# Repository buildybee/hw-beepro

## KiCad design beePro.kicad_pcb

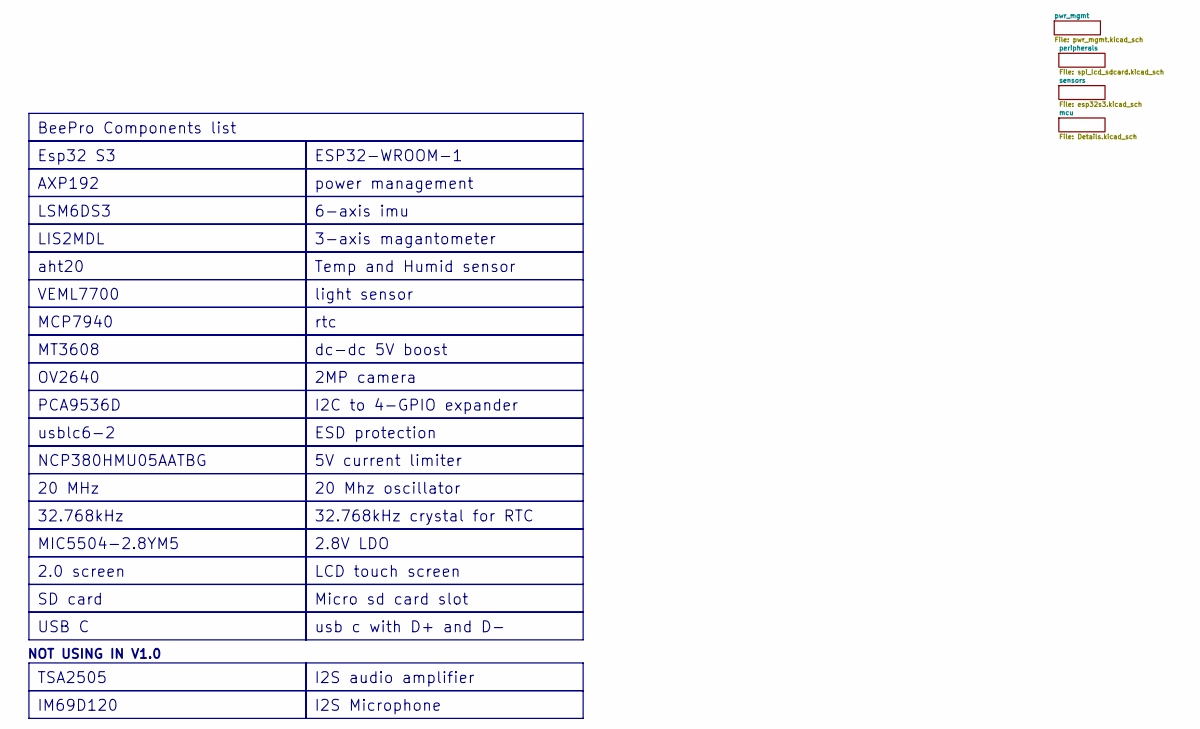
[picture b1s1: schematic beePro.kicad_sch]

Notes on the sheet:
NOT USING IN V1.0
20 Mhz oscillator
OV2640
2.8V LDO
MIC5504-2.8YM5
BeePro Components list
USB C
VEML7700
20 MHz
Micro sd card slot
I2S Microphone
rtc
5V current limiter
power management
light sensor
TSA2505
SD card
I2C to 4-GPIO expander
NCP380HMU05AATBG
LIS2MDL
MCP7940
Esp32 S3
AXP192
I2S audio amplifier
32.768kHz
2.0 screen
usb c with D+ and D-
32.768kHz crystal for RTC
ESP32-WROOM-1
3-axis magantometer
Temp and Humid sensor
6-axis imu
PCA9536D
aht20
ESD protection
MT3608
IM69D120
usblc6-2
2MP camera
dc-dc 5V boost

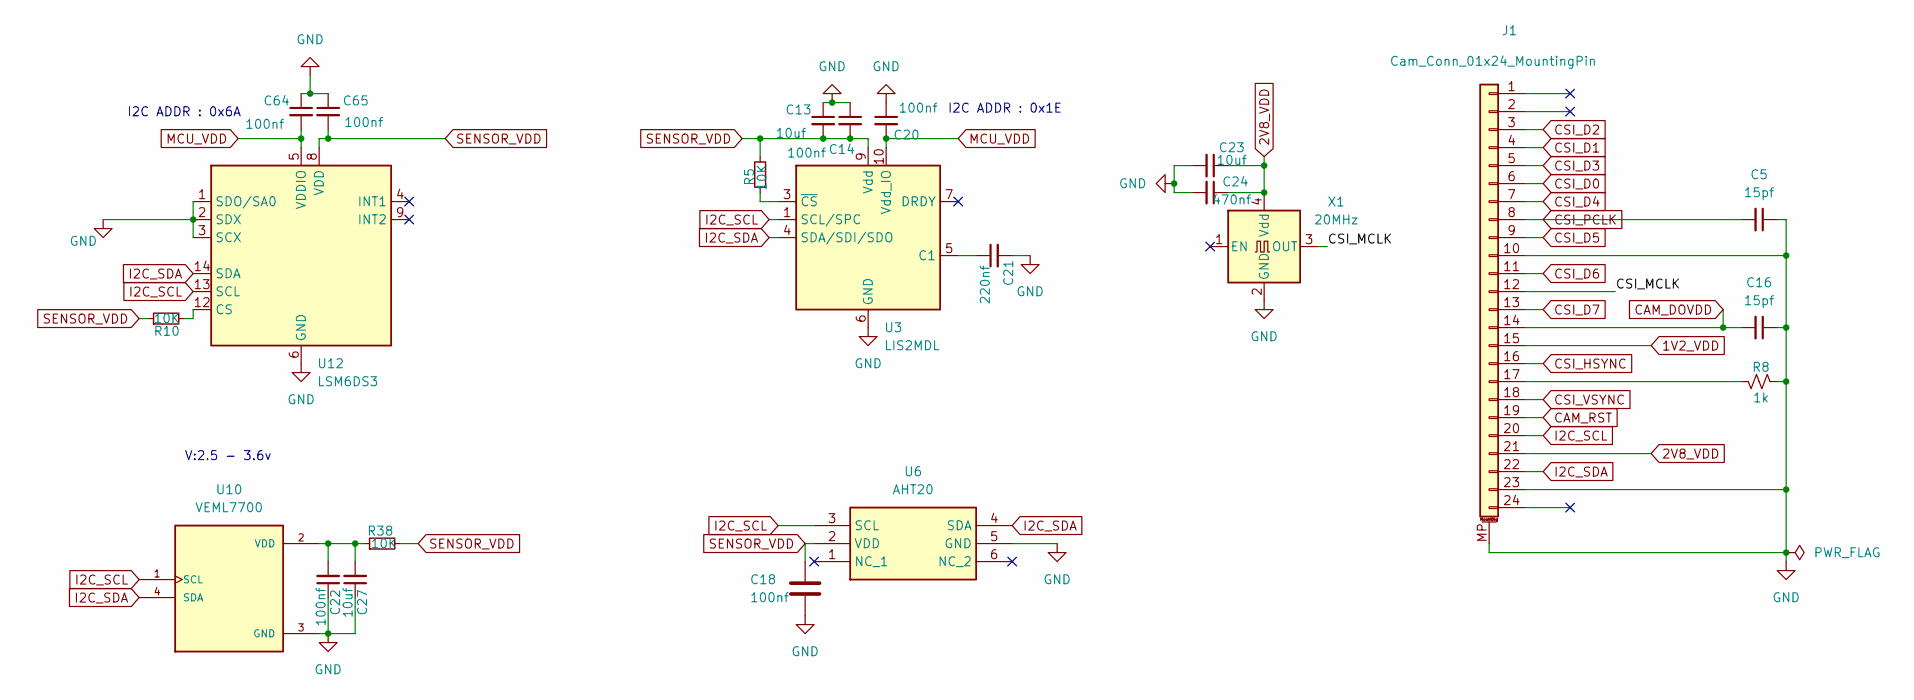
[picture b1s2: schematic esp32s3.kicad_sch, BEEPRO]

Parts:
C5, C16: 15pf; C_0603_1608Metric_Pad1.08x0.95mm_HandSolder
C13, C23, C27: 10uf; C_0603_1608Metric_Pad1.08x0.95mm_HandSolder
C14, C18, C20, C22, C64, C65: 100nf; C_0603_1608Metric_Pad1.08x0.95mm_HandSolder
C21: 220nf; C_0603_1608Metric_Pad1.08x0.95mm_HandSolder
C24: 470nf; C_0603_1608Metric_Pad1.08x0.95mm_HandSolder
J1: Cam_Conn_01x24_MountingPin; Hirose_FH12-24S-0.5SH_1x24-1MP_P0.50mm_Horizontal
R5, R10, R38: 10K; R_0603_1608Metric_Pad0.98x0.95mm_HandSolder
R8: 1k; R_0603_1608Metric_Pad0.98x0.95mm_HandSolder
U3: LIS2MDL; LGA-12_2x2mm_P0.5mm
U6: AHT20; Manufacturer_Part_Number AHT20
U10: VEML7700; XDCR_VEML7700-TR; PARTREV 1.6
U12: LSM6DS3; LGA-14_3x2.5mm_P0.5mm_LayoutBorder3x4y
X1: 20MHz; Oscillator_SMD_Abracon_ASE-4Pin_3.2x2.5mm

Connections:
1V2_VDD: J1.15; also elsewhere on the board
2V8_VDD: C23.1, C24.1, J1.21, X1.4 (Vdd); also elsewhere on the board
/sensors/CSI_MCLK: J1.12, X1.3 (OUT)
CAM_DOVDD: C5.1, C13.1, C13.2, C14.1, C14.2, C16.1, C16.2, C18.1, C18.2, C20.1, C21.2, C22.1, C23.2, C24.2, C27.1, C64.1, C65.1, C65.2, J1.10, J1.14, J1.23, J1.MP (MountPin), R5.2, R8.1, R10.1, R38.2, U3.6 (GND), U3.8 (GND), U3.9 (Vdd), U6.2 (VDD), U6.5 (GND), U10.3 (GND), U12.1 (SDO/SA0), U12.2 (SDX), U12.3 (SCX), U12.6 (GND), U12.7 (GND), U12.8 (VDD), X1.2 (GND); also elsewhere on the board
CAM_RST: J1.19
CSI_D0: J1.6; also elsewhere on the board
CSI_D1: J1.4; also elsewhere on the board
CSI_D2: J1.3; also elsewhere on the board
CSI_D3: J1.5; also elsewhere on the board
CSI_D4: J1.7; also elsewhere on the board
CSI_D5: J1.9; also elsewhere on the board
CSI_D6: J1.11; also elsewhere on the board
CSI_D7: J1.13; also elsewhere on the board
CSI_HSYNC: J1.16; also elsewhere on the board
CSI_PCLK: C5.2, J1.8; also elsewhere on the board
CSI_VSYNC: J1.18; also elsewhere on the board
I2C_SCL: J1.20, U3.1 (SCL/SPC), U6.3 (SCL), U10.1 (SCL), U12.13 (SCL); also elsewhere on the board
I2C_SDA: J1.22, U3.4 (SDA/SDI/SDO), U6.4 (SDA), U10.4 (SDA), U12.14 (SDA); also elsewhere on the board
MCU_VDD: C20.2, C64.2, U3.10 (Vdd_IO), U12.5 (VDDIO); also elsewhere on the board
unnamed: J1.17, R8.2
unnamed: C21.1, U3.5 (C1)
unnamed: R5.1, U3.3 (~CS)
unnamed: C22.2, C27.2, R38.1, U10.2 (VDD)
unnamed: R10.2, U12.12 (CS)

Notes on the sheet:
V:2.5 - 3.6v
I2C ADDR : 0x6A
I2C ADDR : 0x1E

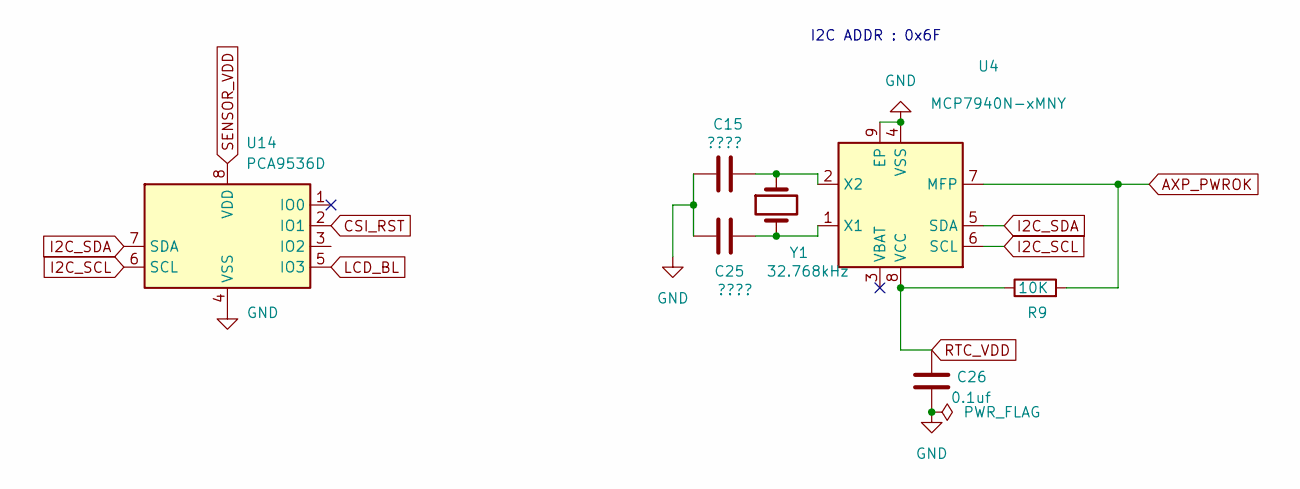
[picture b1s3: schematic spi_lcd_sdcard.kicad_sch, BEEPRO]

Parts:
C15, C25: ????; C_0603_1608Metric_Pad1.08x0.95mm_HandSolder
C26: 0.1uf; C_0603_1608Metric_Pad1.08x0.95mm_HandSolder
R9: 10K; R_0603_1608Metric_Pad0.98x0.95mm_HandSolder
U4: MCP7940N-xMNY; DFN-8-1EP_3x2mm_P0.5mm_EP1.36x1.46mm
U14: PCA9536D; SOIC-8_3.9x4.9mm_P1.27mm
Y1: 32.768kHz; Crystal_SMD_3215-2Pin_3.2x1.5mm

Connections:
AXP_WAKEUP: R9.2, U4.7 (MFP); also elsewhere on the board
CAM_DOVDD: C15.2, C25.1, C26.2, U4.4 (VSS), U4.9 (EP), U14.4 (VSS), U14.8 (VDD); also elsewhere on the board
CSI_RST: U14.2 (IO1)
I2C_SCL: U4.6 (SCL), U14.6 (SCL); also elsewhere on the board
I2C_SDA: U4.5 (SDA), U14.7 (SDA); also elsewhere on the board
LCD_RST: U14.3 (IO2)
unnamed: C25.2, U4.1 (X1), Y1.2
unnamed: C15.1, U4.2 (X2), Y1.1
RTC_VDD: C26.1, R9.1, U4.8 (VCC); also elsewhere on the board

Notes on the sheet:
I2C ADDR : 0x6F

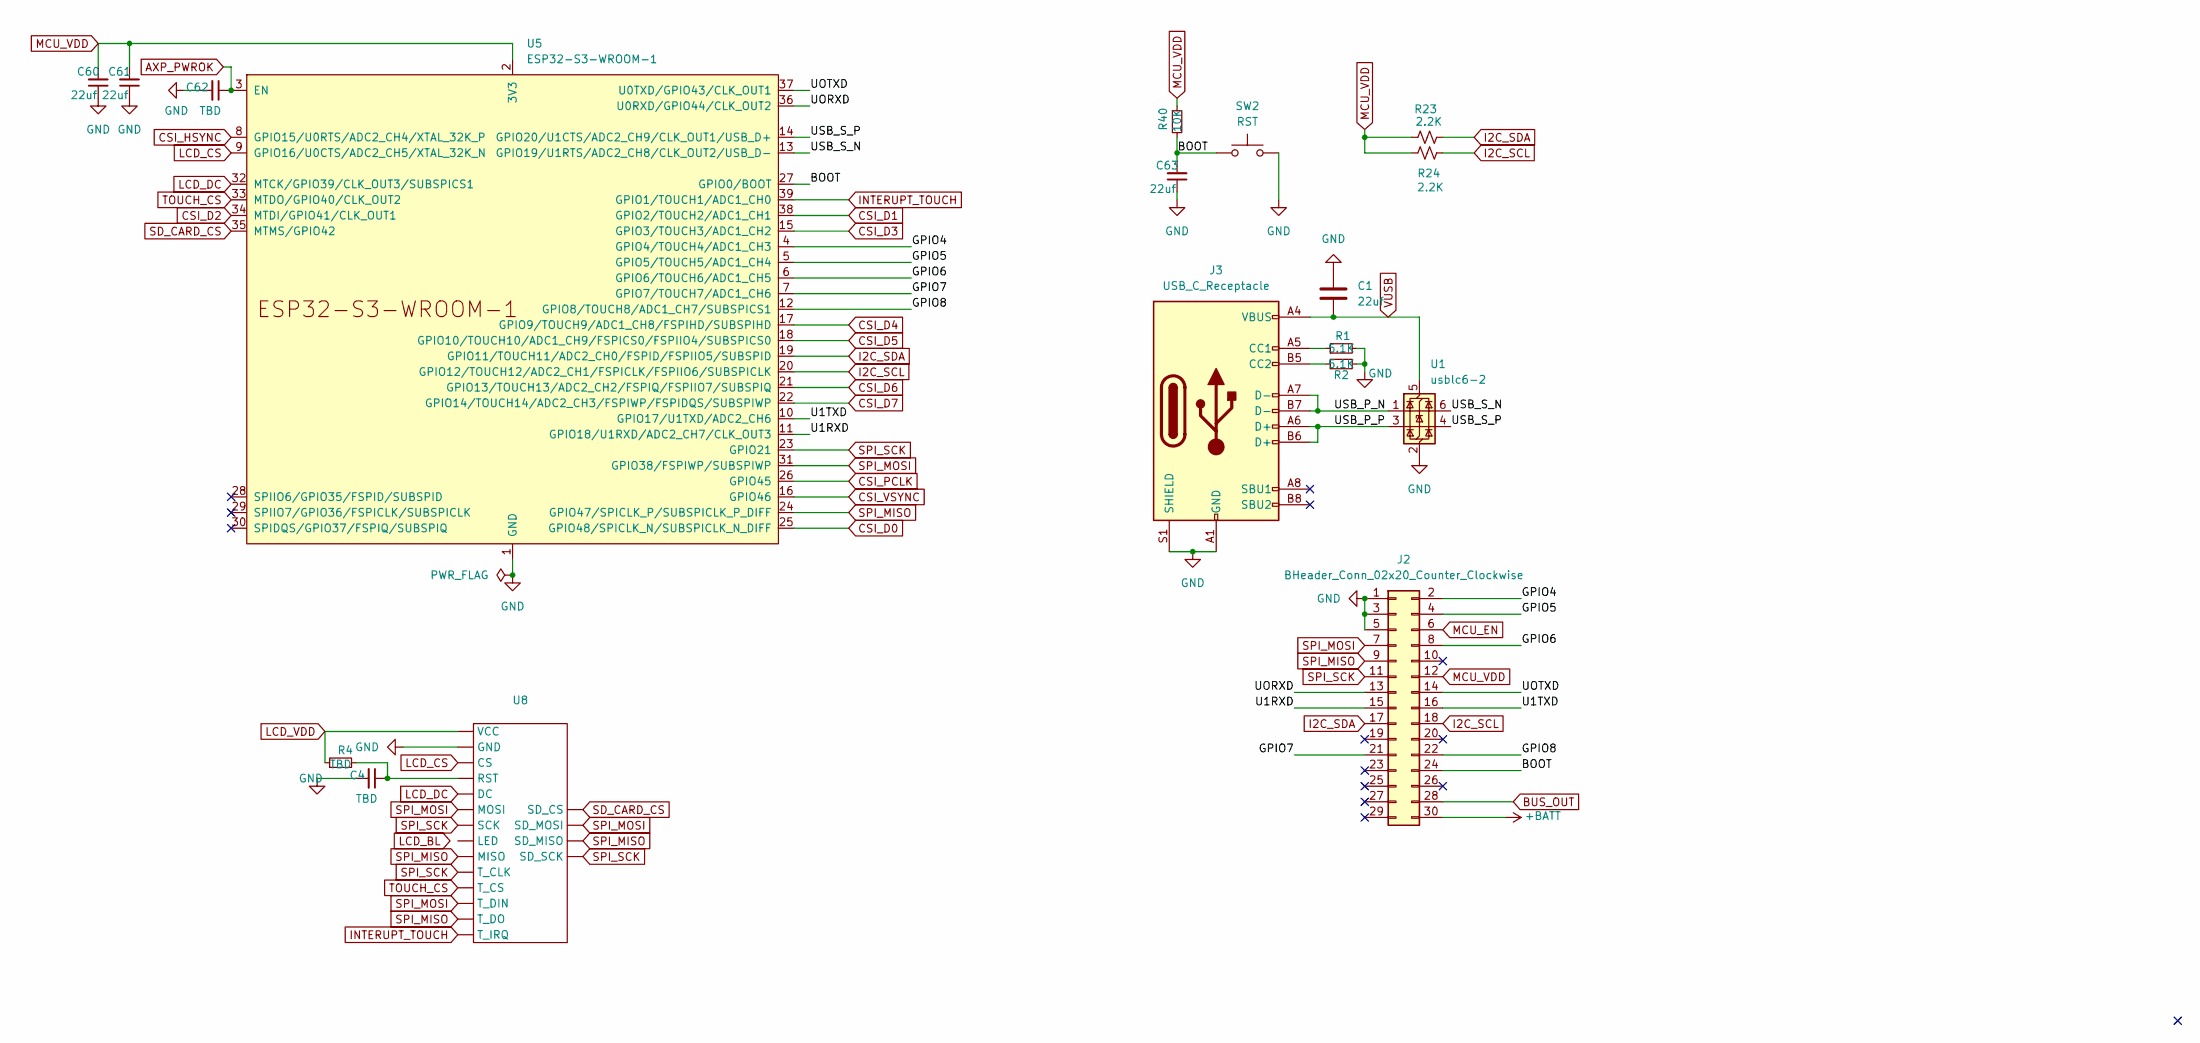
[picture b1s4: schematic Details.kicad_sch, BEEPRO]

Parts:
C1, C60, C61, C63: 22uf; C_0603_1608Metric_Pad1.08x0.95mm_HandSolder
C4, C62: TBD; C_0603_1608Metric_Pad1.08x0.95mm_HandSolder
J2: BHeader_Conn_02x20_Counter_Clockwise; PinSocket_2x15_P2.54mm_Vertical
J3: USB_C_Receptacle; USB_C_Receptacle_GCT_USB4110
R1, R2: 5.1K; R_0603_1608Metric_Pad0.98x0.95mm_HandSolder
R4: TBD; C_0603_1608Metric_Pad1.08x0.95mm_HandSolder
R23, R24: 2.2K; R_0603_1608Metric_Pad0.98x0.95mm_HandSolder
R40: 10K; R_0603_1608Metric_Pad0.98x0.95mm_HandSolder
SW2: RST; SW_SPST_PTS647_Sx38
U1: usblc6-2; SOT-23-6
U5: ESP32-S3-WROOM-1; ESP32-S3-WROOM-1U
U8: (no value)

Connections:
+BATT: J2.30; also elsewhere on the board
/mcu/BOOT: C63.2, J2.24, R40.2, SW2.1, U5.27 (GPIO0/BOOT)
/mcu/GPIO4: J2.2, U5.4 (GPIO4/TOUCH4/ADC1_CH3)
/mcu/GPIO5: J2.4, U5.5 (GPIO5/TOUCH5/ADC1_CH4)
/mcu/GPIO6: J2.8, U5.6 (GPIO6/TOUCH6/ADC1_CH5)
/mcu/GPIO7: J2.21, U5.7 (GPIO7/TOUCH7/ADC1_CH6)
/mcu/GPIO8: J2.22, U5.12 (GPIO8/TOUCH8/ADC1_CH7/SUBSPICS1)
/mcu/U1RXD: J2.15, U5.11 (GPIO18/U1RXD/ADC2_CH7/CLK_OUT3)
/mcu/U1TXD: J2.16, U5.10 (GPIO17/U1TXD/ADC2_CH6)
/mcu/UORXD: J2.13, U5.36 (U0RXD/GPIO44/CLK_OUT2)
/mcu/UOTXD: J2.14, U5.37 (U0TXD/GPIO43/CLK_OUT1)
/mcu/USB_P_N: J3.A7 (D-), J3.B7 (D-), U1.1 (I/O1)
/mcu/USB_P_P: J3.A6 (D+), J3.B6 (D+), U1.3 (I/O2)
/mcu/USB_S_N: U1.6 (I/O1), U5.13 (GPIO19/U1RTS/ADC2_CH8/CLK_OUT2/USB_D-)
/mcu/USB_S_P: U1.4 (I/O2), U5.14 (GPIO20/U1CTS/ADC2_CH9/CLK_OUT1/USB_D+)
BUS_OUT: J2.28; also elsewhere on the board
CAM_DOVDD: C1.1, C4.2, C60.1, C61.1, C62.2, C63.1, J2.1, J2.3, J2.5, J3.A1 (GND), J3.A12 (GND), J3.B1 (GND), J3.B12 (GND), J3.S1 (SHIELD), R1.2, R2.2, SW2.2, U1.2 (GND), U5.1 (GND), U5.40 (GND), U5.41 (GND), U8.; also elsewhere on the board
CSI_D0: U5.25 (GPIO48/SPICLK_N/SUBSPICLK_N_DIFF); also elsewhere on the board
CSI_D1: U5.38 (GPIO2/TOUCH2/ADC1_CH1); also elsewhere on the board
CSI_D2: U5.34 (MTDI/GPIO41/CLK_OUT1); also elsewhere on the board
CSI_D3: U5.15 (GPIO3/TOUCH3/ADC1_CH2); also elsewhere on the board
CSI_D4: U5.17 (GPIO9/TOUCH9/ADC1_CH8/FSPIHD/SUBSPIHD); also elsewhere on the board
CSI_D5: U5.18 (GPIO10/TOUCH10/ADC1_CH9/FSPICS0/FSPIIO4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); also elsewhere on the board
CSI_D6: U5.21 (GPIO13/TOUCH13/ADC2_CH2/FSPIQ/FSPIIO7/S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); also elsewhere on the board
CSI_D7: U5.22 (GPIO14/TOUCH14/ADC2_CH3/FSPIWP/FSPIDQS/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); also elsewhere on the board
CSI_HSYNC: U5.8 (GPIO15/U0RTS/ADC2_CH4/XTAL_32K_P); also elsewhere on the board
CSI_PCLK: U5.26 (GPIO45); also elsewhere on the board
CSI_VSYNC: U5.16 (GPIO46); also elsewhere on the board
I2C_SCL: J2.18, R24.2, U5.20 (GPIO12/TOUCH12/ADC2_CH1/FSPICLK/FSPIIO6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); also elsewhere on the board
I2C_SDA: J2.17, R23.2, U5.19 (GPIO11/TOUCH11/ADC2_CH0/FSPID/FSPIIO5/S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); also elsewhere on the board
INTERUPT_TOUCH: U5.39 (GPIO1/TOUCH1/ADC1_CH0), U8.
LCD_CS: U5.9 (GPIO16/U0CTS/ADC2_CH5/XTAL_32K_N), U8.
LCD_DC: U5.32 (MTCK/GPIO39/CLK_OUT3/SUBSPICS1), U8.
MCU_VDD: C60.2, C61.2, J2.12, R23.1, R24.1, R40.1, U5.2 (3V3); also elsewhere on the board
unnamed: C4.1, R4.2, U8.
unnamed: J3.A5 (CC1), R1.1
unnamed: J3.B5 (CC2), R2.1
unnamed: R4.1, U8.
unnamed 78: C62.1, U5.3 (EN); also elsewhere on the board
SD_CARD_CS: U5.35 (MTMS/GPIO42), U8.
SPI_MISO: J2.9, U5.24 (GPIO47/SPICLK_P/SUBSPICLK_P_DIFF), U8.
SPI_MOSI: J2.7, U5.31 (GPIO38/FSPIWP/SUBSPIWP), U8.
SPI_SCK: J2.11, U5.23 (GPIO21), U8.
TOUCH_CS: U5.33 (MTDO/GPIO40/CLK_OUT2), U8.
VUSB: C1.2, J3.A4 (VBUS), J3.A9 (VBUS), J3.B4 (VBUS), J3.B9 (VBUS), U1.5 (VBUS); also elsewhere on the board

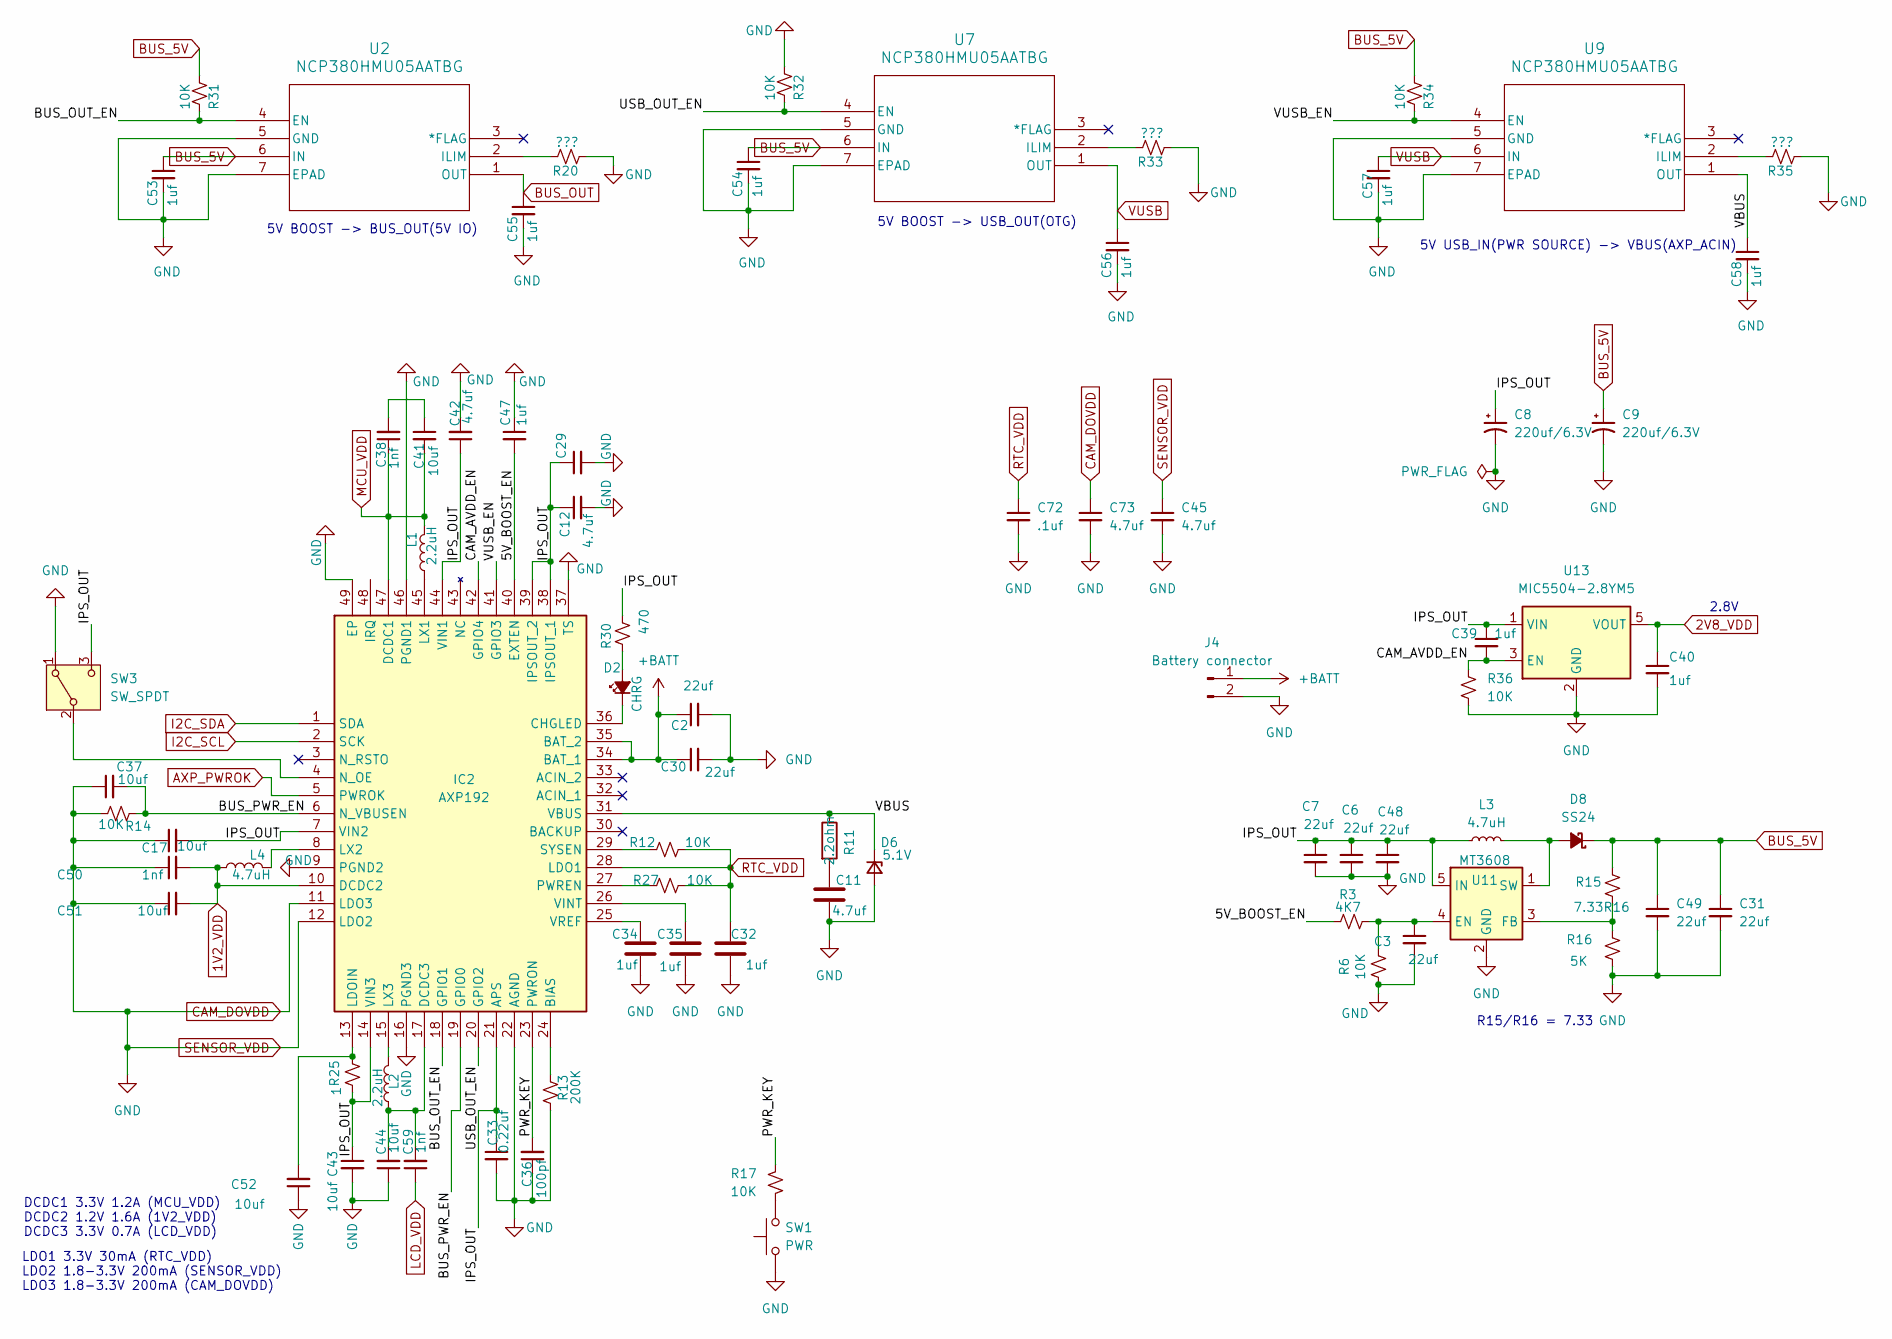
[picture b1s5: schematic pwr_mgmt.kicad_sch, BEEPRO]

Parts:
C2, C3, C6, C7, C30, C31, C48, C49: 22uf; C_0603_1608Metric_Pad1.08x0.95mm_HandSolder
C8, C9: 220uf/6.3V; CP_Elec_6.3x5.3
C11, C12, C29, C42, C45, C73: 4.7uf; C_0603_1608Metric_Pad1.08x0.95mm_HandSolder
C17, C37, C41, C43, C44, C51, C52: 10uf; C_0603_1608Metric_Pad1.08x0.95mm_HandSolder
C32, C34, C35, C39, C40, C47, C53, C54, C55, C56, C57, C58: 1uf; C_0603_1608Metric_Pad1.08x0.95mm_HandSolder
C33: 0.22uf; C_0603_1608Metric_Pad1.08x0.95mm_HandSolder
C36: 100pf; C_0603_1608Metric_Pad1.08x0.95mm_HandSolder
C38, C50, C59: 1nf; C_0603_1608Metric_Pad1.08x0.95mm_HandSolder
C72: .1uf; C_0603_1608Metric_Pad1.08x0.95mm_HandSolder
D2: CHRG; LED_0603_1608Metric_Pad1.05x0.95mm_HandSolder
D6: 5.1V; D_SOD-123
D8: SS24; D_SMA
IC2: AXP192; QFN40P600X600X92-49N-D; Manufacturer_Part_Number AXP192
J4: Battery connector; JST_PH_B2B-PH-K_1x02_P2.00mm_Vertical
L1, L2: 2.2uH; L_Cenker_CKCS252012
L3: 4.7uH; L_Changjiang_FNR5012S
L4: 4.7uH; L_Cenker_CKCS252012
R3: 4K7; R_0603_1608Metric_Pad0.98x0.95mm_HandSolder
R6, R12, R14, R17, R27, R31, R32, R34, R36: 10K; R_0603_1608Metric_Pad0.98x0.95mm_HandSolder
R11: 2.2ohm; R_0603_1608Metric_Pad0.98x0.95mm_HandSolder
R13: 200K; R_0603_1608Metric_Pad0.98x0.95mm_HandSolder
R15: 7.33R16; R_0603_1608Metric_Pad0.98x0.95mm_HandSolder
R16: 5K; R_0603_1608Metric_Pad0.98x0.95mm_HandSolder
R20, R33, R35: ???; R_0603_1608Metric_Pad0.98x0.95mm_HandSolder
R25: 1; R_2512_6332Metric
R30: 470; R_0603_1608Metric_Pad0.98x0.95mm_HandSolder
SW1: PWR; SW_SPST_PTS647_Sx38
SW3: SW_SPDT
U2, U7, U9: NCP380HMU05AATBG; UDFN6_2X2_ONS
U11: MT3608; SOT-23-6
U13: MIC5504-2.8YM5; SOT-23-5

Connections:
1V2_VDD: C50.2, C51.2, IC2.10 (DCDC2), L4.2; also elsewhere on the board
2V8_VDD: C40.1, U13.5 (VOUT); also elsewhere on the board
+BATT: C2.1, C30.1, IC2.34 (BAT_1), IC2.35 (BAT_2), J4.1; also elsewhere on the board
/pwr_mgmt/5V_BOOST_EN: C47.2, IC2.40 (EXTEN), R3.1
/pwr_mgmt/BUS_OUT_EN: IC2.18 (GPIO1), R31.1, U2.4 (EN)
/pwr_mgmt/BUS_PWR_EN: C37.2, IC2.6 (N_VBUSEN), IC2.19 (GPIO0), R14.1
/pwr_mgmt/CAM_AVDD_EN: C39.2, IC2.42 (GPIO4), R36.1, U13.3 (EN)
/pwr_mgmt/IPS_OUT: C6.1, C7.1, C8.1, C12.1, C17.2, C29.1, C33.1, C39.1, C42.1, C43.1, C48.1, IC2.7 (VIN2), IC2.14 (VIN3), IC2.21 (APS), IC2.38 (IPSOUT_1), IC2.39 (IPSOUT_2), IC2.44 (VIN1), L3.1, R25.2, R30.1, SW3.3 (C), U11.5 (IN), U13.1 (VIN)
/pwr_mgmt/PWR_KEY: C36.2, IC2.23 (PWRON), R17.1
/pwr_mgmt/USB_OUT_EN: IC2.20 (GPIO2), R32.1, U7.4 (EN)
/pwr_mgmt/VBUS: C58.1, D6.1 (K), IC2.31 (VBUS), R11.1, U9.1 (OUT)
/pwr_mgmt/VUSB_EN: IC2.41 (GPIO3), R34.1, U9.4 (EN)
AXP_WAKEUP: IC2.48 (IRQ); also elsewhere on the board
BUS_5V: C9.1, C31.1, C49.1, C53.1, C54.1, D8.1 (K), R15.1, R31.2, R34.2, U2.6 (IN), U7.6 (IN)
BUS_OUT: C55.1, U2.1 (OUT); also elsewhere on the board
CAM_DOVDD: C2.2, C3.2, C6.2, C7.2, C8.2, C9.2, C11.2, C12.2, C17.1, C29.2, C30.2, C31.2, C32.2, C33.2, C34.2, C35.2, C36.1, C37.1, C40.2, C42.2, C43.2, C44.1, C45.1, C45.2, C47.1, C48.2, C49.2, C50.1, C51.1, C52.1, C53.2, C54.2, C55.2, C56.2, C57.2, C58.2, C72.2, C73.1, C73.2, D6.2 (A), IC2.4 (N_OE), IC2.9 (PGND2), IC2.11 (LDO3), IC2.12 (LDO2), IC2.16 (PGND3), IC2.22 (AGND), IC2.37 (TS), IC2.46 (PGND1), IC2.49 (EP), J4.2, R6.2, R13.2, R14.2, R16.2, R20.2, R32.2, R33.2, R35.2, R36.2, SW1.1, SW3.1 (A), SW3.2 (B), U2.5 (GND), U2.7 (EPAD), U7.5 (GND), U7.7 (EPAD), U9.5 (GND), U9.7 (EPAD), U11.2 (GND), U13.2 (GND); also elsewhere on the board
I2C_SCL: IC2.2 (SCK); also elsewhere on the board
I2C_SDA: IC2.1 (SDA); also elsewhere on the board
LCD_VDD: C59.1
MCU_VDD: C38.1, C41.2, IC2.47 (DCDC1), L1.1; also elsewhere on the board
unnamed: C11.1, R11.2
unnamed: C38.2, C41.1
unnamed: D2.2 (A), R30.2
unnamed: D2.1 (K), IC2.36 (CHGLED)
unnamed: D8.2 (A), L3.2, U11.1 (SW)
unnamed: IC2.24 (BIAS), R13.1
unnamed: C44.2, C59.2, IC2.17 (DCDC3), L2.1
unnamed: C52.2, IC2.13 (LDOIN), R25.1
unnamed: IC2.45 (LX1), L1.2
unnamed: IC2.8 (LX2), L4.1
unnamed: IC2.15 (LX3), L2.2
unnamed: IC2.27 (PWREN), R27.1
unnamed: IC2.29 (SYSEN), R12.1
unnamed: C35.1, IC2.26 (VINT)
unnamed: C34.1, IC2.25 (VREF)
unnamed: R17.2, SW1.2
unnamed: R20.1, U2.2 (ILIM)
unnamed: R33.1, U7.2 (ILIM)
unnamed: R35.1, U9.2 (ILIM)
unnamed: C3.1, R3.2, R6.1, U11.4 (EN)
unnamed: R15.2, R16.1, U11.3 (FB)
RTC_VDD: C32.1, C72.1, IC2.28 (LDO1), R12.2, R27.2; also elsewhere on the board
VUSB: C56.1, C57.1, U7.1 (OUT), U9.6 (IN); also elsewhere on the board

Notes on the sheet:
5V BOOST -> BUS_OUT(5V IO)
DCDC1 3.3V 1.2A (MCU_VDD) DCDC2 1.2V 1.6A (1V2_VDD) DCDC3 3.3V 0.7A (LCD_VDD)
R15/R16 = 7.33
2.8V
5V USB_IN(PWR SOURCE) -> VBUS(AXP_ACIN)
LDO1 3.3V 30mA (RTC_VDD) LDO2 1.8-3.3V 200mA (SENSOR_VDD) LDO3 1.8-3.3V 200mA (CAM_DOVDD)
5V BOOST -> USB_OUT(OTG)

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
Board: 4 copper layers, 122 parts (84 on the bottom side), 82 nets, no tracks yet.

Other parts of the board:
R18: 2k2; R_0603_1608Metric_Pad0.98x0.95mm_HandSolder
R37: TBD; C_0603_1608Metric_Pad1.08x0.95mm_HandSolder

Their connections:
I2C_SDA: R18.2; also elsewhere on the board
MCU_VDD: R18.1, R37.1; also elsewhere on the board
unnamed 78: R37.2; also elsewhere on the board

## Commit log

2024-04-21 ignore
2024-06-04 inital commit
